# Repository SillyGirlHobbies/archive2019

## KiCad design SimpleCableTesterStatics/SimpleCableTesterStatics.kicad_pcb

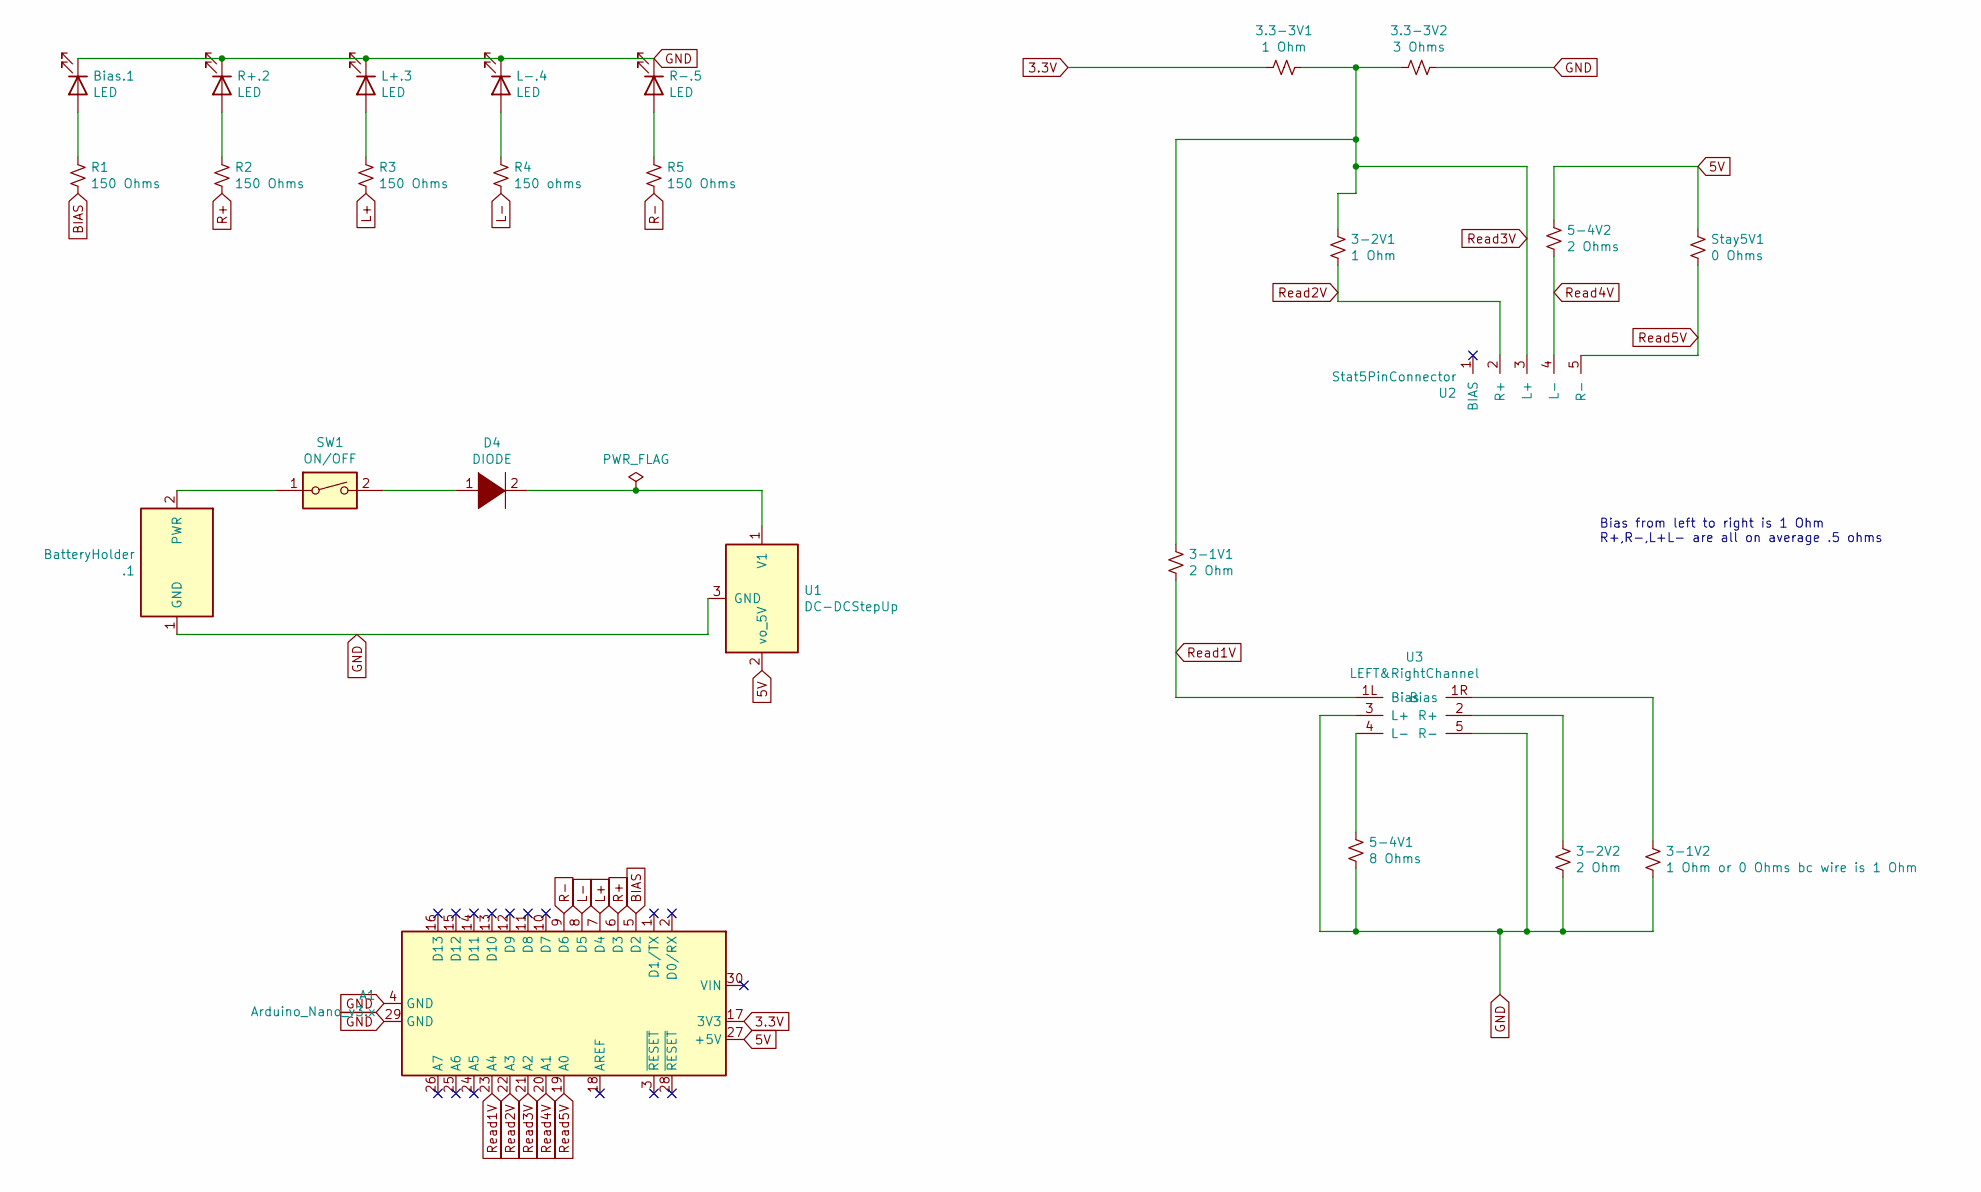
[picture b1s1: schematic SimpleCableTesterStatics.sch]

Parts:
3-1V1, 3-2V2: 2 Ohm; R_Axial_DIN0207_L6.3mm_D2.5mm_P7.62mm_Horizontal
3-1V2: 1 Ohm or 0 Ohms bc wire is 1 Ohm; R_Axial_DIN0207_L6.3mm_D2.5mm_P7.62mm_Horizontal
3-2V1, 3.3-3V1: 1 Ohm; R_Axial_DIN0207_L6.3mm_D2.5mm_P7.62mm_Horizontal
3.3-3V2: 3 Ohms; R_Axial_DIN0207_L6.3mm_D2.5mm_P7.62mm_Horizontal
5-4V1: 8 Ohms; R_Axial_DIN0207_L6.3mm_D2.5mm_P7.62mm_Horizontal
5-4V2: 2 Ohms; R_Axial_DIN0207_L6.3mm_D2.5mm_P7.62mm_Horizontal
.1: BatteryHolder; BAT_BH123A
A1: Arduino_Nano_v3.x; Arduino_Nano
Bias.1: LED; LED_D5.0mm
D4: DIODE; SD0805S020S1R0
L+.3: LED; LED_D5.0mm
L-.4: LED; LED_D5.0mm
R1, R2, R3, R5: 150 Ohms; R_Axial_DIN0207_L6.3mm_D2.5mm_P7.62mm_Horizontal
R4: 150 ohms; R_Axial_DIN0207_L6.3mm_D2.5mm_P7.62mm_Horizontal
R+.2: LED; LED_D5.0mm
R-.5: LED; LED_D5.0mm
SW1: ON/OFF; Switch
Stay5V1: 0 Ohms; R_Axial_DIN0207_L6.3mm_D2.5mm_P7.62mm_Horizontal
U1: DC-DCStepUp; FanPinHeader_1x03_P2.54mm_Vertical
U2: Stat5PinConnector; Static5pinConnector
U3: LEFT&RightChannel; Left&rightChannel

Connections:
3.3V: 3.3-3V1.1, A1.17 (3V3)
5V: 5-4V2.1, A1.27 (+5V), Stay5V1.1, U1.2 (vo_5V)
BIAS: A1.5 (D2), R1.2
GND: 3-1V2.2, 3-2V2.2, 3.3-3V2.2, 5-4V1.2, .1.1 (GND), A1.4 (GND), A1.29 (GND), Bias.1.1 (K), L+.3.1 (K), L-.4.1 (K), R+.2.1 (K), R-.5.1 (K), U1.3 (GND), U3.3 (L+), U3.5 (R-)
L+: A1.7 (D4), R3.2
L-: A1.8 (D5), R4.2
unnamed: 3-1V2.1, U3.1R (Bias)
unnamed: 3-2V2.1, U3.2 (R+)
unnamed: 5-4V1.1, U3.4 (L-)
unnamed: .1.2 (PWR), SW1.1
unnamed: Bias.1.2 (A), R1.1
unnamed: D4.1 (K), SW1.2
unnamed: D4.2 (A), U1.1 (V1)
unnamed: L+.3.2 (A), R3.1
unnamed: L-.4.2 (A), R4.1
unnamed: R2.1, R+.2.2 (A)
unnamed: R5.1, R-.5.2 (A)
R+: A1.6 (D3), R2.2
R-: A1.9 (D6), R5.2
Read1V: 3-1V1.2, A1.23 (A4), U3.1L (Bias)
Read2V: 3-2V1.2, A1.22 (A3), U2.2 (R+)
Read3V: 3-1V1.1, 3-2V1.1, 3.3-3V1.2, 3.3-3V2.1, A1.21 (A2), U2.3 (L+)
Read4V: 5-4V2.2, A1.20 (A1), U2.4 (L-)
Read5V: A1.19 (A0), Stay5V1.2, U2.5 (R-)

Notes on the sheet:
Bias from left to right is 1 Ohm R+,R-,L+L- are all on average .5 ohms

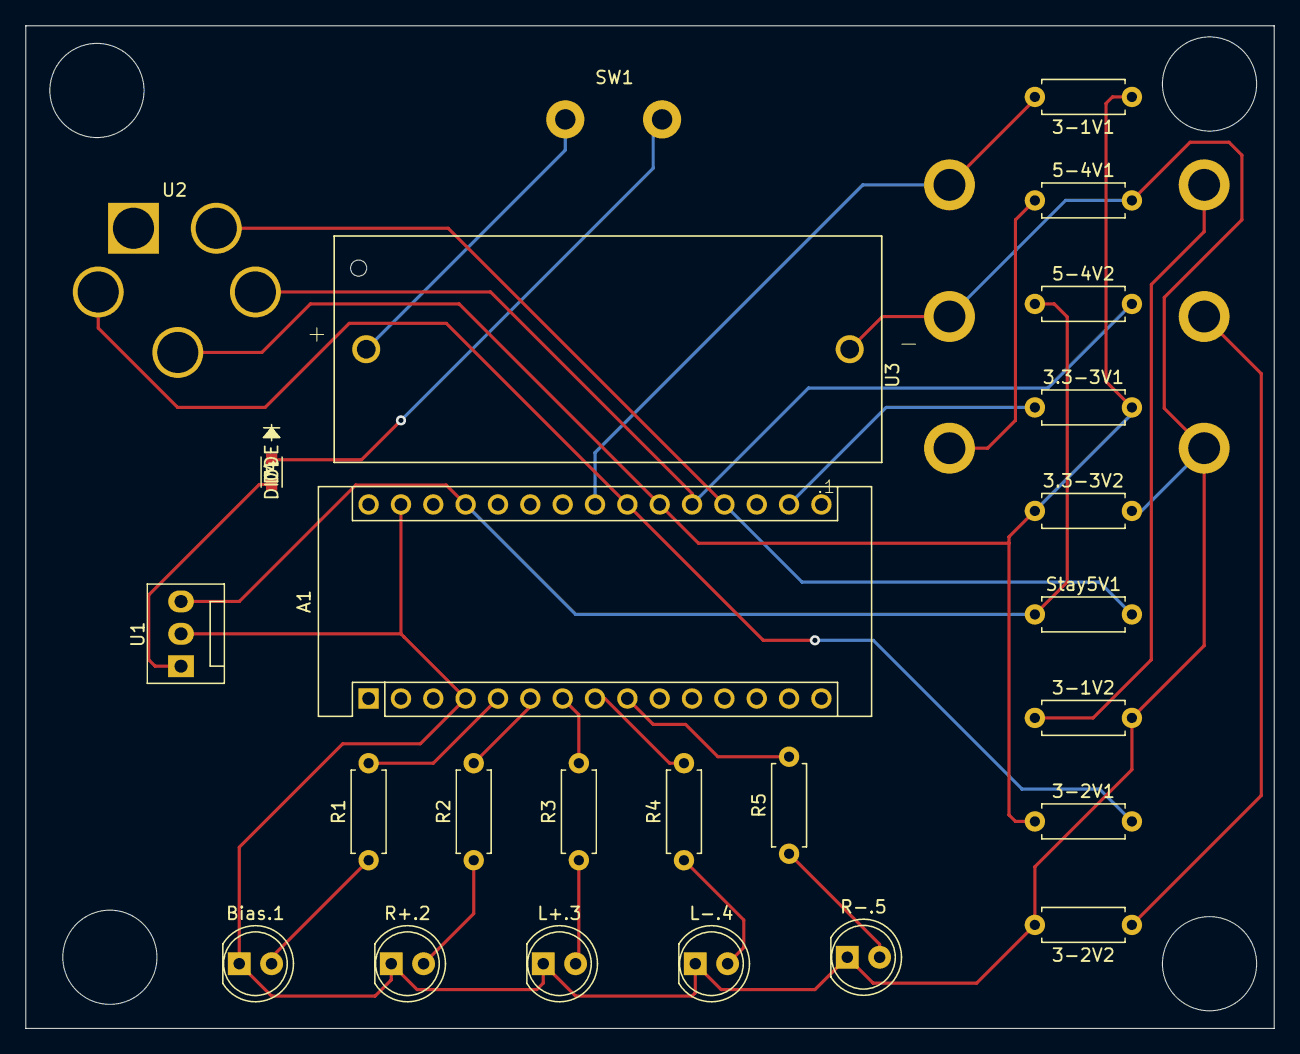
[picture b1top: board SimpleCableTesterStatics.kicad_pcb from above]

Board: 2 copper layers, 98.0 x 78.7 mm, 26 parts (0 on the bottom side), 24 nets.

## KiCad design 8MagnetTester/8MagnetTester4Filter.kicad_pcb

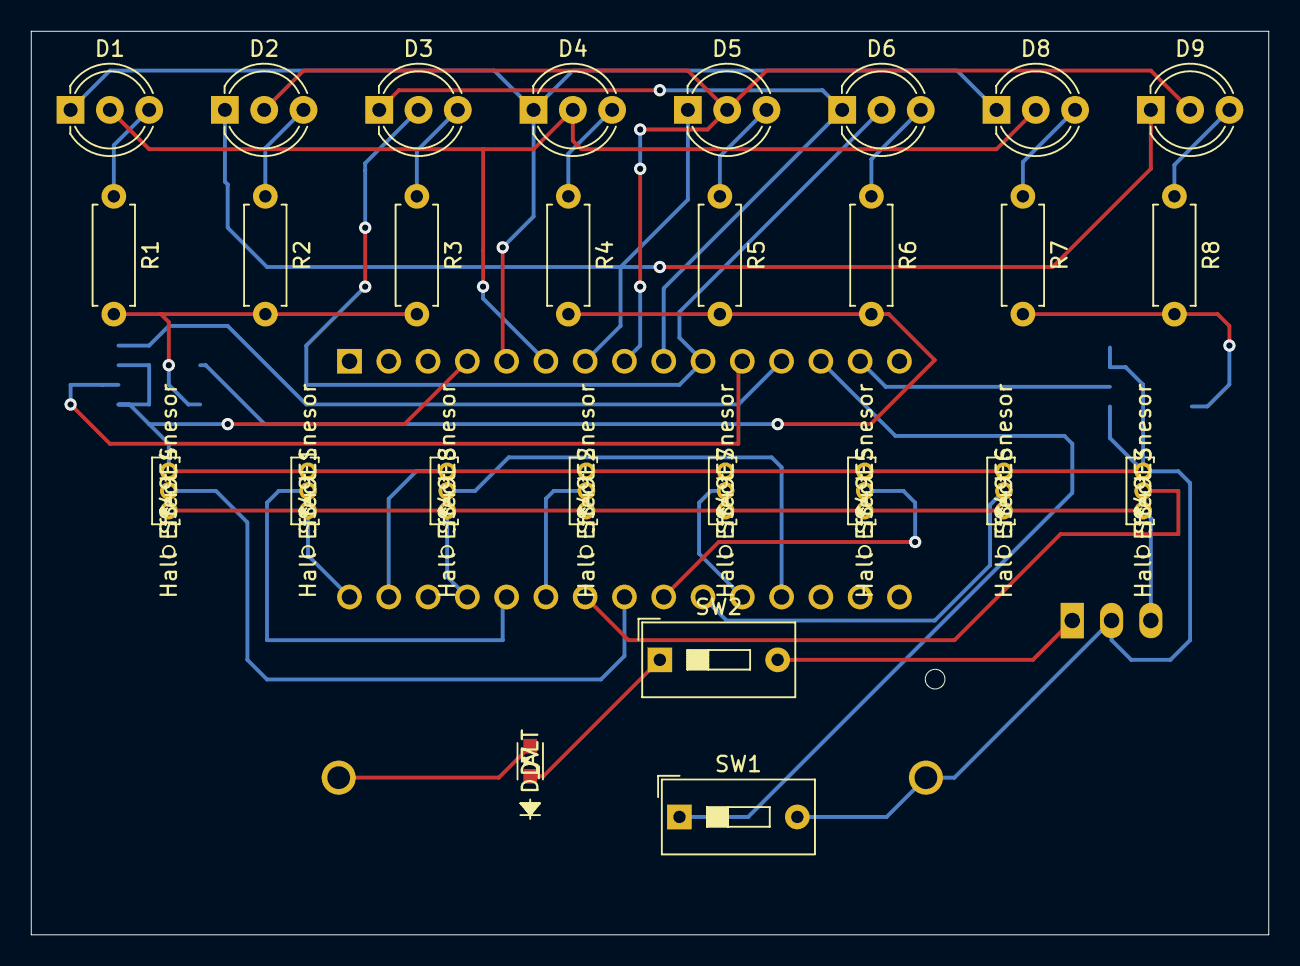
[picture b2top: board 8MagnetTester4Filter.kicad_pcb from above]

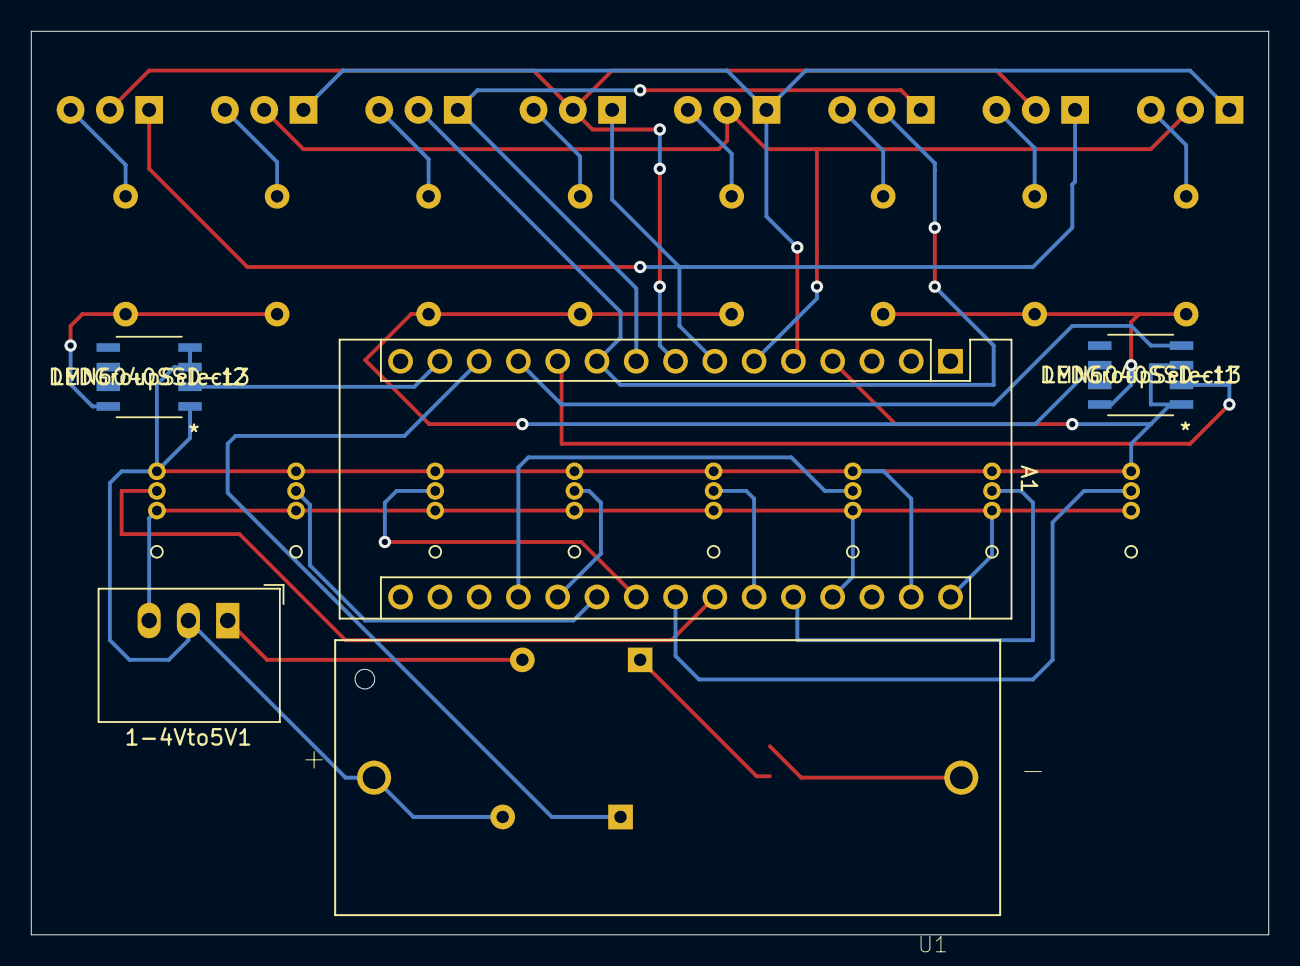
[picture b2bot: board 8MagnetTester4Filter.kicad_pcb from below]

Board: 2 copper layers, 80.0 x 58.4 mm, 32 parts (5 on the bottom side), 34 nets.

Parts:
1-4Vto5V1: StepUpConverter; Converter_DCDC_RECOM_R-78E-0.5_THT
A1: Arduino_Nano_v2.x; Arduino_Nano
D1, D2, D3, D4, D5, D6, D8, D9: LED_Dual_AAC; LED_D5.0mm-3
D7: D_ALT; SD0805S020S1R0
LEDGroupSelect1, LEDGroupSelect2: DMN6040SSD-13; DMN6040SSS-13
R1, R2, R3, R4, R5, R6, R7, R8: 150R; R_Axial_DIN0207_L6.3mm_D2.5mm_P7.62mm_Horizontal
SS49E1, SS49E2, SS49E3, SS49E4, SS49E5, SS49E6, SS49E7, SS49E8: Hall Effect Snesor; SS49E
SW1: SW_SPST; SW_DIP_SPSTx01_Slide_9.78x4.72mm_W7.62mm_P2.54mm
SW2: SW_Reed; SW_DIP_SPSTx01_Slide_9.78x4.72mm_W7.62mm_P2.54mm
U1: BatteryHolder; BAT_BH123A

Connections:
5V: 1-4Vto5V1.3, A1.27, A1.30, SS49E1.1, SS49E2.1, SS49E3.1, SS49E4.1, SS49E5.1, SS49E6.1, SS49E7.1, SS49E8.1
A0: A1.19, SS49E8.2
A1: A1.20, SS49E7.2
A2: A1.21, SS49E6.2
A3: A1.22, SS49E5.2
A4: A1.23, SS49E4.2
A5: A1.24, SS49E3.2
A6: A1.25, SS49E2.2
A7: A1.26, SS49E1.2
D2: A1.5, D1.1, D4.1, D8.1
D3: A1.6, D1.2, D4.2, D8.2
D4: A1.7, D2.1, D5.1, D9.1
D5: A1.8, D2.2, D5.2, D9.2
D6: A1.9, D3.1, D6.1
D7: A1.10, D3.2, D6.2
D8: A1.11, LEDGroupSelect1.2
D9: A1.12, LEDGroupSelect1.4
D10: A1.13, SW1.1
D11: A1.14, LEDGroupSelect2.2
GND: 1-4Vto5V1.2, A1.4, A1.29, LEDGroupSelect1.1, LEDGroupSelect1.3, LEDGroupSelect2.1, LEDGroupSelect2.3, LEDGroupSelect2.4, SS49E1.3, SS49E2.3, SS49E3.3, SS49E4.3, SS49E5.3, SS49E6.3, SS49E7.3, SS49E8.3, SW1.2, U1.2
unnamed: 1-4Vto5V1.1, SW2.2
unnamed: D1.3, R1.1
unnamed: D2.3, R2.1
unnamed: D3.3, R3.1
unnamed: D4.3, R4.1
unnamed: D5.3, R5.1
unnamed: D6.3, R6.1
unnamed: D7.1, SW2.1
unnamed: D7.2, U1.1
unnamed: D8.3, R7.1
unnamed: D9.3, R8.1
unnamed: LEDGroupSelect1.6, R4.2, R5.2, R6.2
unnamed: LEDGroupSelect1.8, R1.2, R2.2, R3.2
unnamed: LEDGroupSelect2.8, R7.2, R8.2

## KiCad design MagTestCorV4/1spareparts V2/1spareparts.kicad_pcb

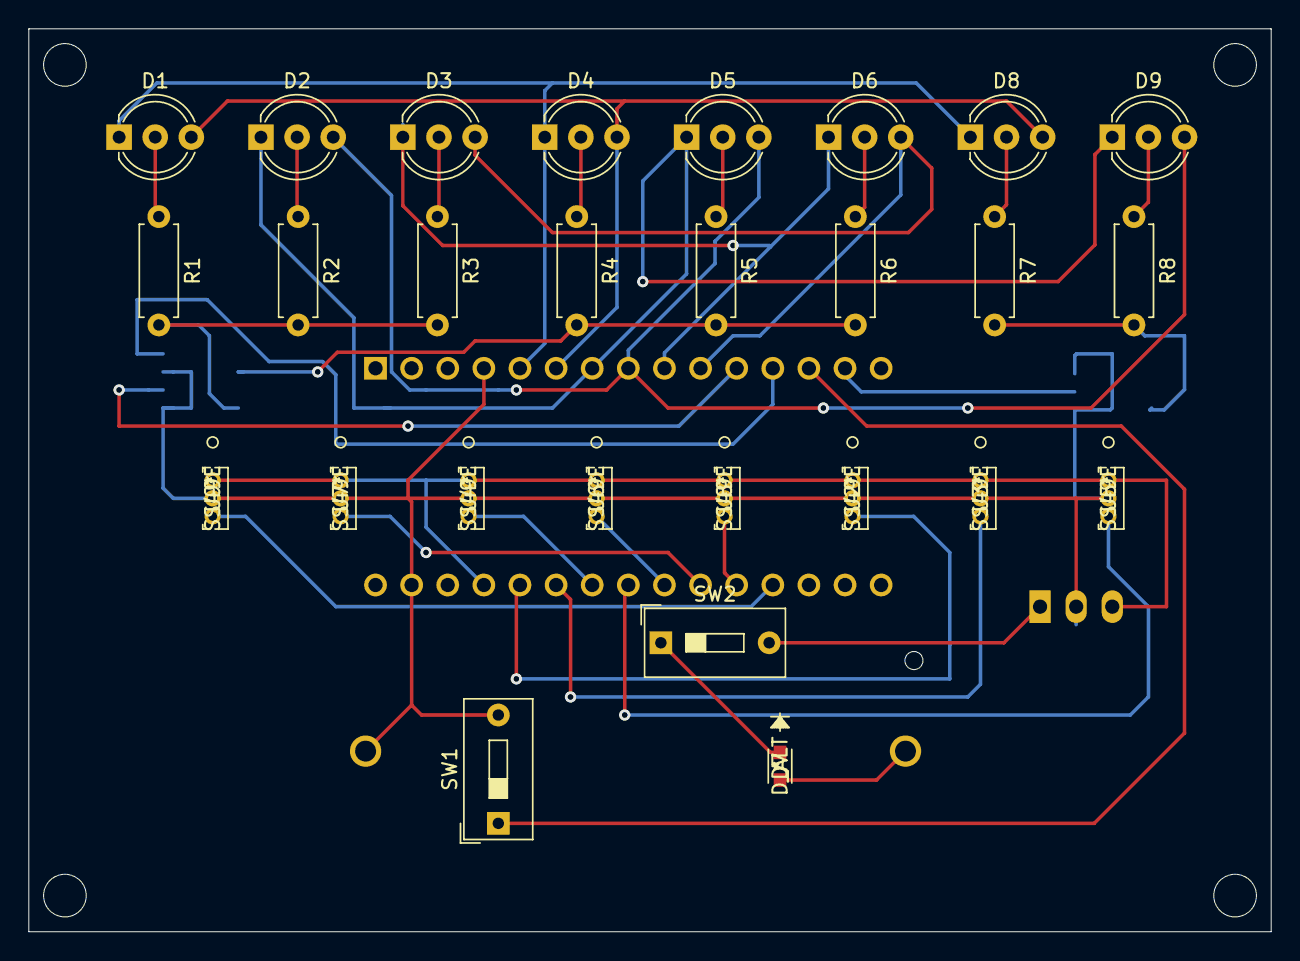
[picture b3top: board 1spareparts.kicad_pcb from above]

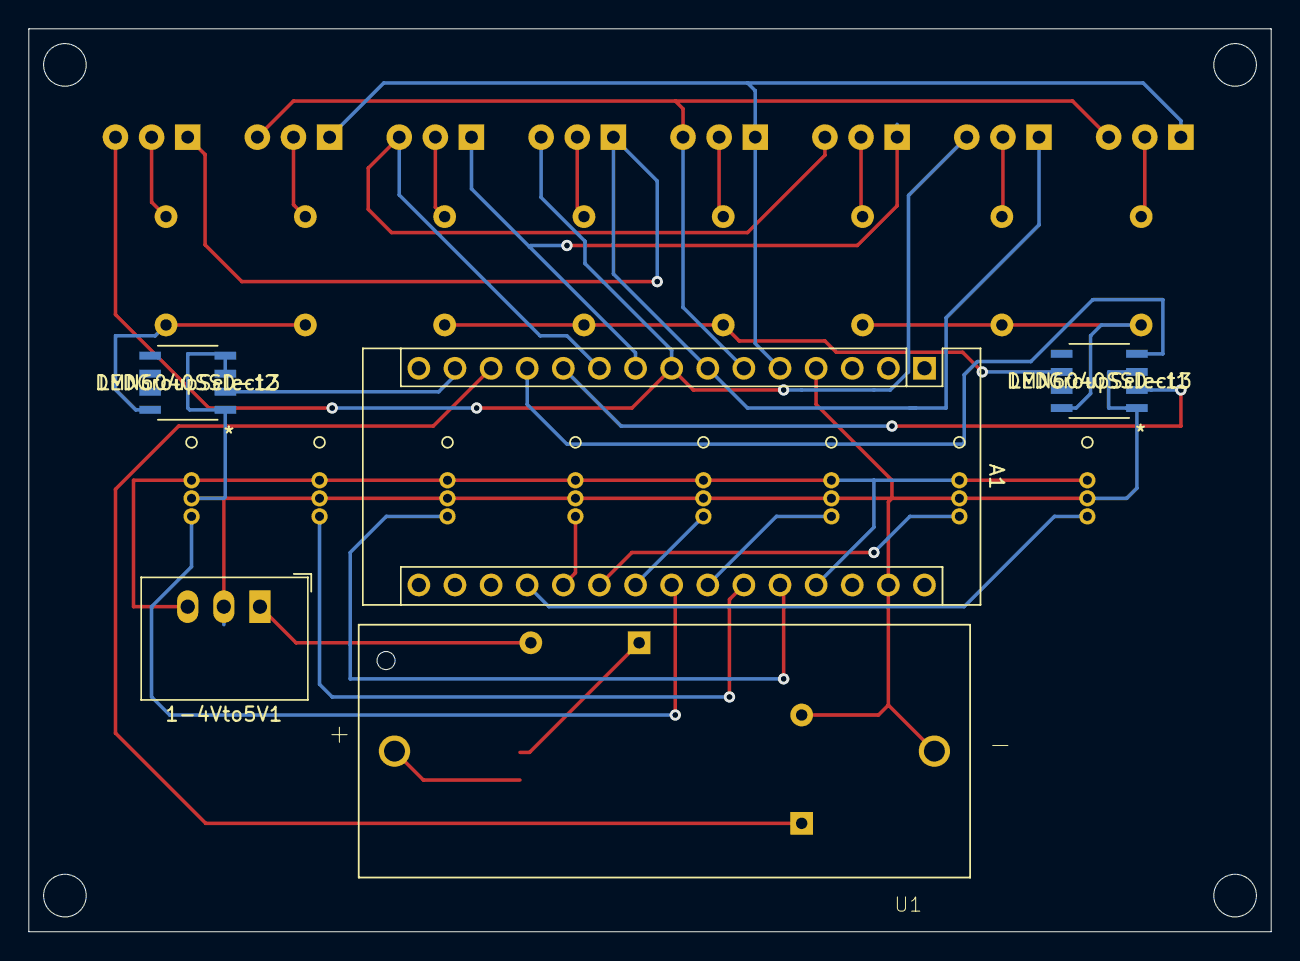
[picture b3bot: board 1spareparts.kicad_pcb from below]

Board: 2 copper layers, 87.4 x 63.5 mm, 32 parts (5 on the bottom side), 34 nets.

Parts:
1-4Vto5V1: StepUpConverter; Converter_DCDC_RECOM_R-78E-0.5_THT
A1: Arduino_Nano_v2.x; Arduino_Nano
D1, D2, D3, D4, D5, D6, D8, D9: LED_Dual_AAC; LED_D5.0mm-3
D7: D_ALT; SD0805S020S1R0
LEDGroupSelect1, LEDGroupSelect2: DMN6040SSD-13; DMN6040SSS-13
R1, R2, R3, R4, R5, R6, R7, R8: 150R; R_Axial_DIN0207_L6.3mm_D2.5mm_P7.62mm_Horizontal
SW1: SW_SPST; SW_DIP_SPSTx01_Slide_9.78x4.72mm_W7.62mm_P2.54mm
SW2: SW_Reed; SW_DIP_SPSTx01_Slide_9.78x4.72mm_W7.62mm_P2.54mm
U1: BatteryHolder; BAT_BH123A
U2, U3, U4, U5, U6, U7, U8, U9: SS49E

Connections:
5V: 1-4Vto5V1.3, A1.27, U2.1, U3.1, U4.1, U5.1, U6.1, U7.1, U8.1, U9.1
A0: A1.19, U9.3
A1: A1.20, U8.3
A2: A1.21, U7.3
A3: A1.22, U6.3
A4: A1.23, U5.3
A5: A1.24, U4.3
A6: A1.25, U3.3
A7: A1.26, U2.3
D2: A1.5, D1.1, D4.1, D8.1
D3: A1.6, D1.3, D4.3, D8.3
D4: A1.7, D2.1, D5.1, D9.1
D5: A1.8, D2.3, D5.3, D9.3
D6: A1.9, D3.1, D6.1
D7: A1.10, D3.3, D6.3
D8: A1.11, LEDGroupSelect1.2
D9: A1.12, LEDGroupSelect1.4
D10: A1.13, SW1.1
D11: A1.14, LEDGroupSelect2.2
GND: 1-4Vto5V1.2, A1.4, A1.29, LEDGroupSelect1.1, LEDGroupSelect1.3, LEDGroupSelect2.1, LEDGroupSelect2.3, LEDGroupSelect2.4, SW1.2, U1.1, U2.2, U3.2, U4.2, U5.2, U6.2, U7.2, U8.2, U9.2
unnamed: 1-4Vto5V1.1, SW2.2
unnamed: D1.2, R1.1
unnamed: D2.2, R2.1
unnamed: D3.2, R3.1
unnamed: D4.2, R4.1
unnamed: D5.2, R5.1
unnamed: D6.2, R6.1
unnamed: D7.1, SW2.1
unnamed: D7.2, U1.2
unnamed: D8.2, R7.1
unnamed: D9.2, R8.1
unnamed: LEDGroupSelect1.6, R4.2, R5.2, R6.2
unnamed: LEDGroupSelect1.8, R1.2, R2.2, R3.2
unnamed: LEDGroupSelect2.8, R7.2, R8.2

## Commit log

2025-06-10 Delete MagTester8HEffect directory
    -
2025-06-10 Delete FilterMagnetTestCurrentV1/FilterMagTstExperiment directory
    =

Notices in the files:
parts and their libraries:
Copyright 2021 Accelerated Designs. All rights reserved.
